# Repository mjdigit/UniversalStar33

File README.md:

# UniversalStar33

UniversalStar33 is a compact ortholinear lowprofile keyboard with 33 keys and a TPS43
touchpad.

UniversalStar33は小型のタッチパッドを中央に配置した、33キーオーソリニアレイアウトのコンパクトなロープロファイルキーボードです。

## Parts List

### Parts need to be prepared/purchased

|Part|Quantity|Remarks|
|---|---|---|
|Wired controller board<br/>コントローラボード|1|RP2040-Zero (w/ pin headers)|
|Choc socket|33|e.g. Kailh PG1350 KeySwitches Contact (CPG135001S30)|
|Choc V2 switch|33||
|1U Keycap|33||
|Touchpad Module TPS43 (or clone module)|1||
|Polycarbonate sheet for touchpad (0.5mm thickness)<br/>or any other sheet for putting on the touchpad|1|Need to be cut to suit TPS65|
|PET double-sided adhesive sheet<br/>両面接着シート|1|Need to be cut to suit TPS65|
|M2 Spacer (3.5mm-)|4|Spacers for between main plate and touchpad mounting plate|
|M2 Spacer (5.0mm)|6|Spacers for between top plate and bottom plate.|
|M2 screw (3.0-3.5mm)|8|-|
|M2 screw (3.5-4.0mm)|12|-|
|FPC cable (6pin, 0.5mm pitch, 50mm length)|1|-|
|Rubber feet<br/>ゴム足|6|-|

### Parts need to be ordered/printed

|Part|Remarks|
|---|---|
|Main PCB|<image src="images/plate-main.png" height="100px"><br/>gerber/UniversalStar33_Asemble.zip<br/>Needs PCBA for Diodes, Resistor, Capacitor and FPC socket|
|Top Plate|<image src="images/plate-top.png" height="100px"><br/>gerber/top.zip|
|Bottom plate|<image src="images/plate-bottom.png" height="100px"><br/>gerber/bottom.zip|
|Touchpad mounting plate|<image src="images/plate-touchpad.png" height="100px"><br/>gerber/touchpad.zip|

## Build Guide
T.B.D.

## QMK Firmware
T.B.D.

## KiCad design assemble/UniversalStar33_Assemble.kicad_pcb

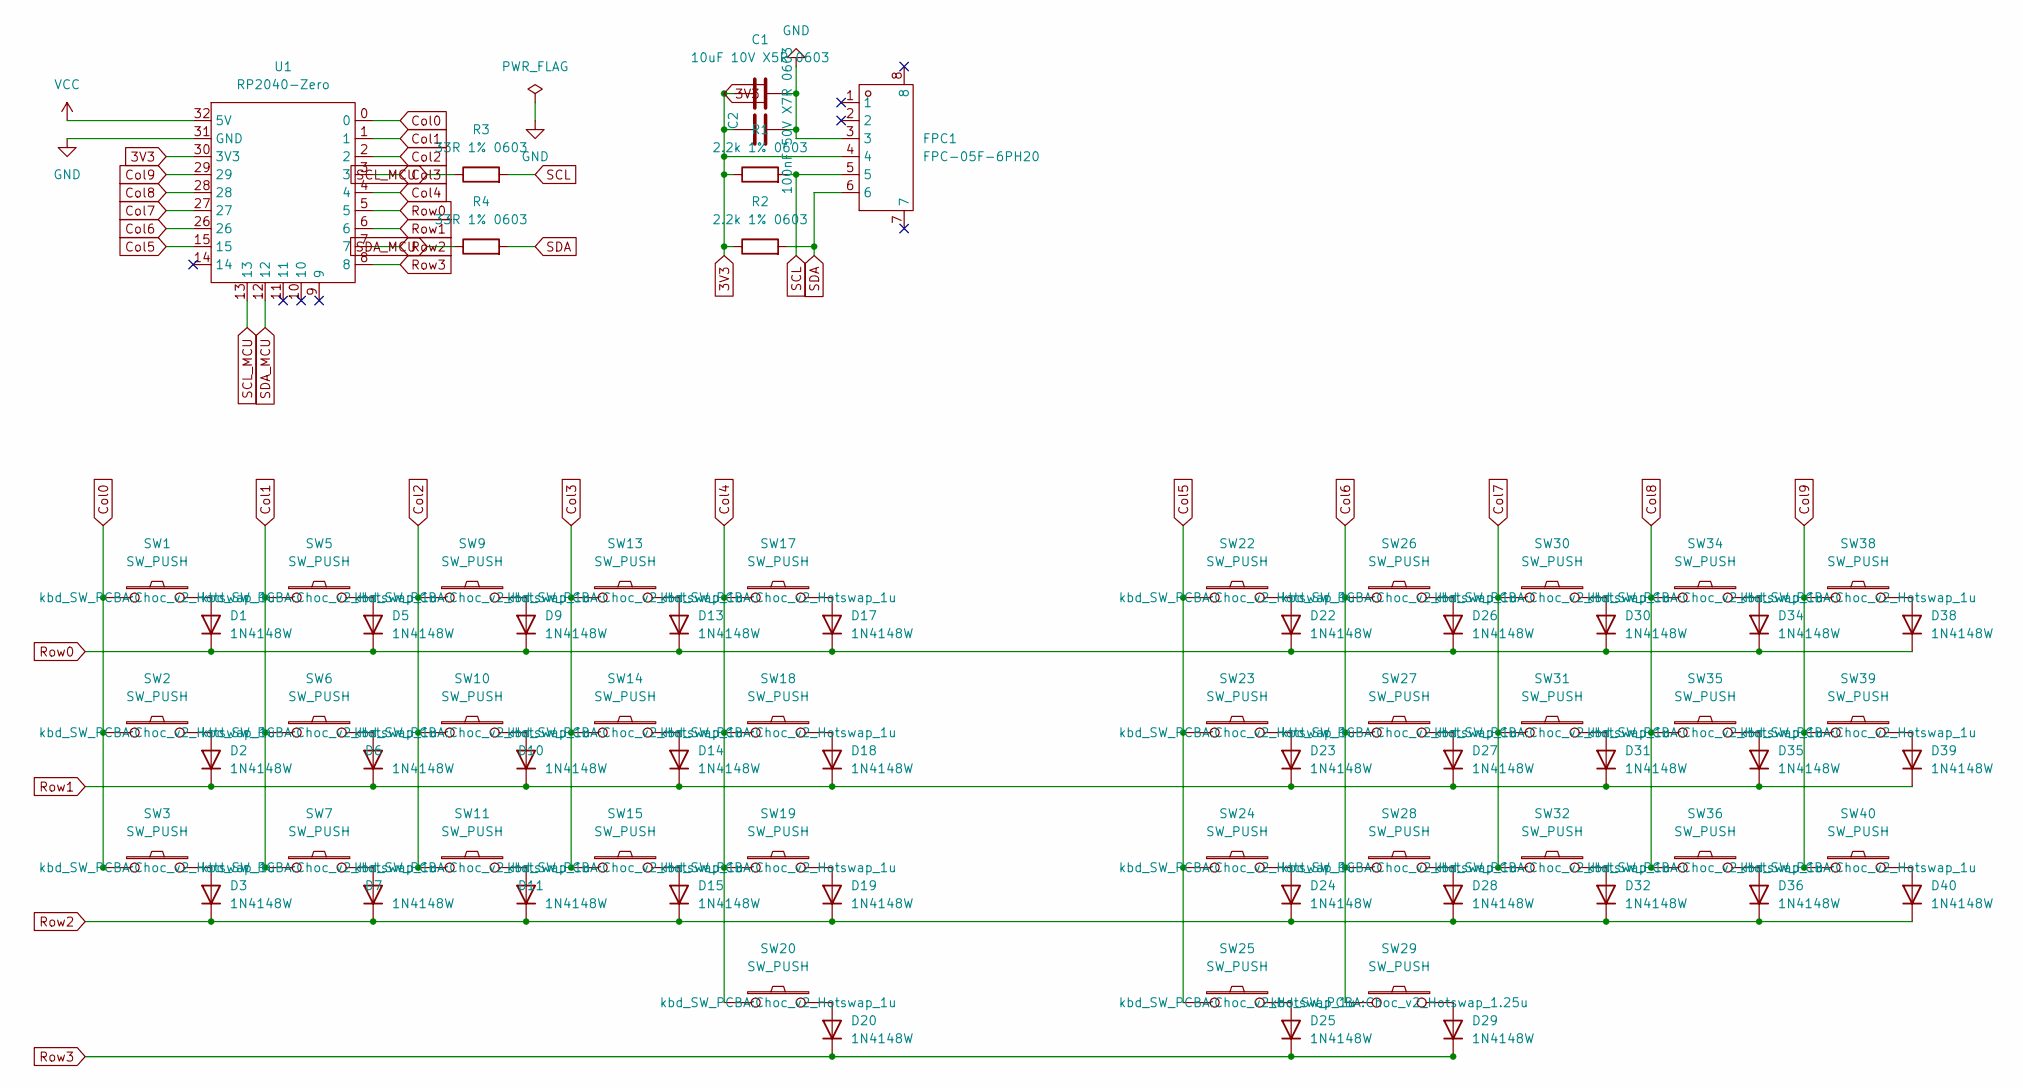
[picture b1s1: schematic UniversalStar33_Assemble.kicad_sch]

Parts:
C1: 10uF 10V X5R 0603; C_0603_1608Metric; Manufacturer Part CL10A106KP8NNNC; LCSC Part # C19702
C2: 100nF 50V X7R 0603; C_0603_1608Metric; Manufacturer Part CC0603KRX7R9BB104; LCSC Part # C14663
D1, D2, D3, D5, D6, D7, D9, D10, D11, D13, D14, D15, D17, D18, D19, D20, D22, D23, D24, D25, D26, D27, D28, D29, D30, D31, D32, D34, D35, D36, D38, D39, D40: 1N4148W; D_SOD-123; Manufacturer Part 1N4148W; LCSC Part # C81598
FPC1: FPC-05F-6PH20; Manufacturer Part FPC-05F-6PH20; LCSC Part Name 翻盖式 卧贴 P数:6P 间距:0.5mm
R1, R2: 2.2k 1% 0603; R_0603_1608Metric; Manufacturer Part 0603WAF2201T5E; LCSC Part # C4190
R3, R4: 33R 1% 0603; R_0603_1608Metric; Manufacturer Part 0603WAF330JT5E; LCSC Part # C23140
SW1, SW2, SW3, SW5, SW6, SW7, SW9, SW10, SW11, SW13, SW14, SW15, SW17, SW18, SW19, SW20, SW22, SW23, SW24, SW25, SW26, SW27, SW28, SW30, SW31, SW32, SW34, SW35, SW36, SW38, SW39, SW40: SW_PUSH; Choc_v2_Hotswap_1u
SW29: SW_PUSH; Choc_v2_Hotswap_1.25u
U1: RP2040-Zero; RP2040-Zero-THT-SMD

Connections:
3V3: C1.1, C2.1, FPC1.4, R1.1, R2.1, U1.30 (3V3)
Col0: SW1.1, SW2.1, SW3.1, U1.0
Col1: SW5.1, SW6.1, SW7.1, U1.1
Col2: SW9.1, SW10.1, SW11.1, U1.2
Col3: SW13.1, SW14.1, SW15.1, U1.3
Col4: SW17.1, SW18.1, SW19.1, SW20.1, U1.4
Col5: SW22.1, SW23.1, SW24.1, SW25.1, U1.15
Col6: SW26.1, SW27.1, SW28.1, SW29.1, U1.26
Col7: SW30.1, SW31.1, SW32.1, U1.27
Col8: SW34.1, SW35.1, SW36.1, U1.28
Col9: SW38.1, SW39.1, SW40.1, U1.29
GND: C1.2, C2.2, FPC1.3, U1.31 (GND)
unnamed: D1.2 (A), SW1.2
unnamed: D2.2 (A), SW2.2
unnamed: D3.2 (A), SW3.2
unnamed: D5.2 (A), SW5.2
unnamed: D6.2 (A), SW6.2
unnamed: D7.2 (A), SW7.2
unnamed: D9.2 (A), SW9.2
unnamed: D10.2 (A), SW10.2
unnamed: D11.2 (A), SW11.2
unnamed: D13.2 (A), SW13.2
unnamed: D14.2 (A), SW14.2
unnamed: D15.2 (A), SW15.2
unnamed: D17.2 (A), SW17.2
unnamed: D18.2 (A), SW18.2
unnamed: D19.2 (A), SW19.2
unnamed: D20.2 (A), SW20.2
unnamed: D22.2 (A), SW22.2
unnamed: D23.2 (A), SW23.2
unnamed: D24.2 (A), SW24.2
unnamed: D25.2 (A), SW25.2
unnamed: D26.2 (A), SW26.2
unnamed: D27.2 (A), SW27.2
unnamed: D28.2 (A), SW28.2
unnamed: D29.2 (A), SW29.2
unnamed: D30.2 (A), SW30.2
unnamed: D31.2 (A), SW31.2
unnamed: D32.2 (A), SW32.2
unnamed: D34.2 (A), SW34.2
unnamed: D35.2 (A), SW35.2
unnamed: D36.2 (A), SW36.2
unnamed: D38.2 (A), SW38.2
unnamed: D39.2 (A), SW39.2
unnamed: D40.2 (A), SW40.2
Row0: D1.1 (K), D5.1 (K), D9.1 (K), D13.1 (K), D17.1 (K), D22.1 (K), D26.1 (K), D30.1 (K), D34.1 (K), D38.1 (K), U1.5
Row1: D2.1 (K), D6.1 (K), D10.1 (K), D14.1 (K), D18.1 (K), D23.1 (K), D27.1 (K), D31.1 (K), D35.1 (K), D39.1 (K), U1.6
Row2: D3.1 (K), D7.1 (K), D11.1 (K), D15.1 (K), D19.1 (K), D24.1 (K), D28.1 (K), D32.1 (K), D36.1 (K), D40.1 (K), U1.7
Row3: D20.1 (K), D25.1 (K), D29.1 (K), U1.8
SCL: FPC1.5, R1.2, R3.2
SCL_MCU: R3.1, U1.13
SDA: FPC1.6, R2.2, R4.2
SDA_MCU: R4.1, U1.12
VCC: U1.32 (5V)

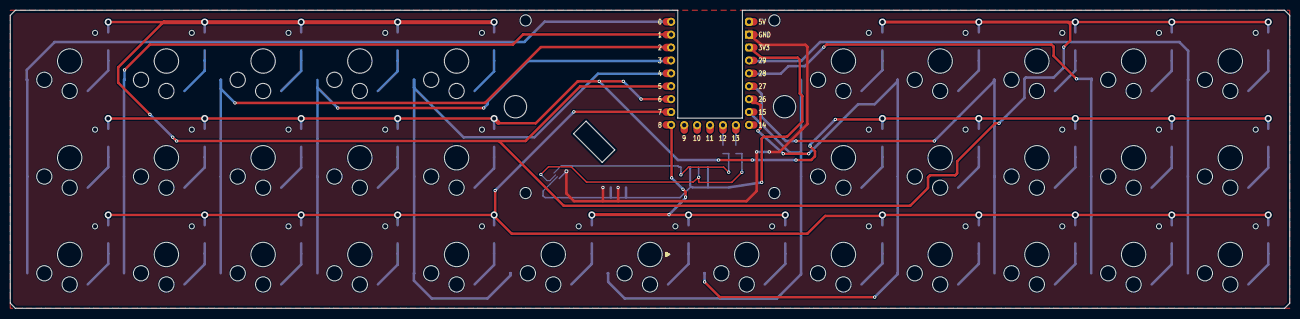
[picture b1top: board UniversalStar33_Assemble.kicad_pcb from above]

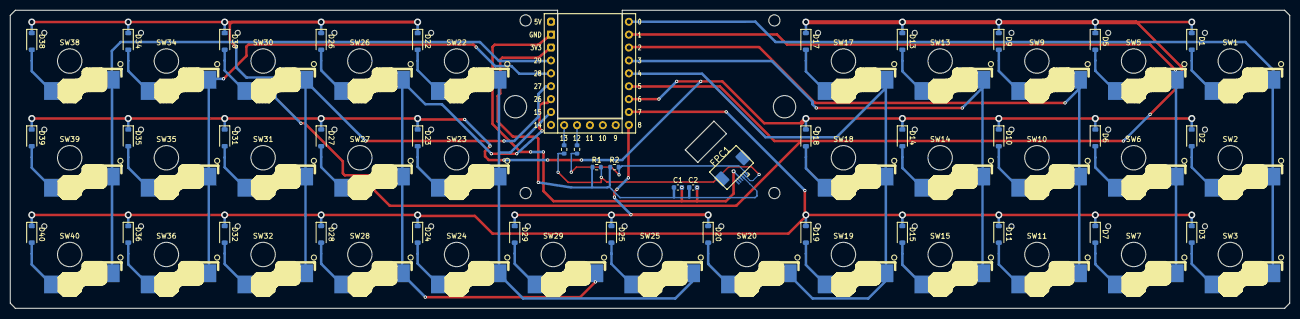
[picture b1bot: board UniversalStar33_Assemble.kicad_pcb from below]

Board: 2 copper layers, 252.0 x 58.7 mm, 80 parts (74 on the bottom side), 53 nets.

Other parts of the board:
Ref**: M2_ScrewHole
Ref**#2, Ref**#4: M2_SpacerHole
Ref**#3, Ref**#5, Ref**#6: M2_ScrewHole
